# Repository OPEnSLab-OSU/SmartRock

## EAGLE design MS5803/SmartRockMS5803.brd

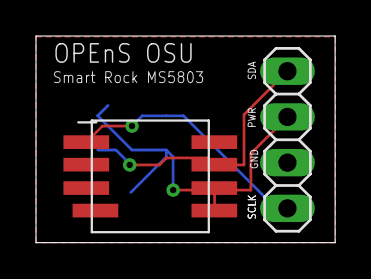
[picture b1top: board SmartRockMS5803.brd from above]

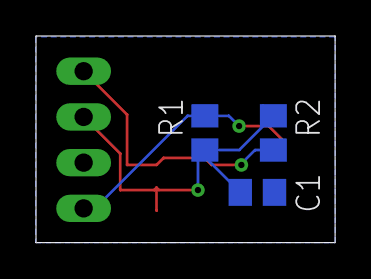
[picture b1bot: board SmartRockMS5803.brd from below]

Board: 2 copper layers, 16.6 x 11.5 mm, 5 parts (3 on the bottom side), 4 nets.

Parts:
C1: 100nF; C0805
JP1: 1X04
PRESSURE: MS5803-01BA; SMD
R1, R2: 7.7k; R0805

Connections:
GND: C1.1, JP1.3, PRESSURE.CSB, PRESSURE.GND
unnamed: C1.2, JP1.2, PRESSURE.PS, PRESSURE.VDD, R1.2, R2.2
unnamed: JP1.1, PRESSURE.SDI/SDA, R2.1
SCLK: JP1.4, PRESSURE.SCLK, R1.1

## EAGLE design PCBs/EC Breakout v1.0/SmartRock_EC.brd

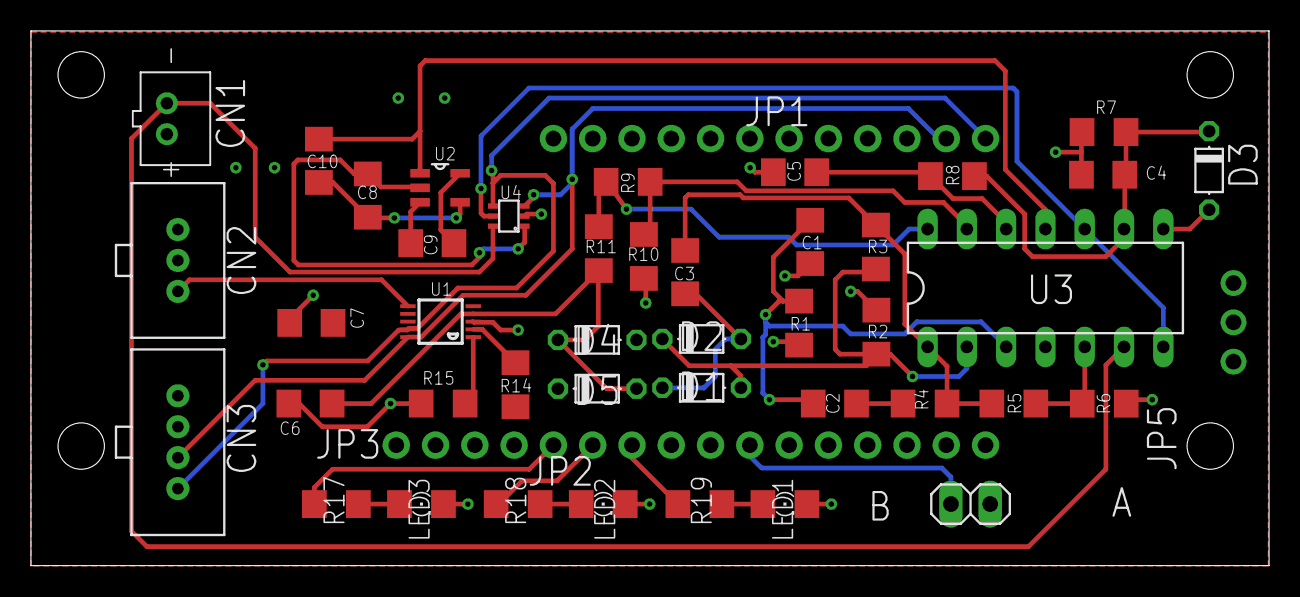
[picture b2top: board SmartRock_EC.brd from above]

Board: 2 copper layers, 80.0 x 34.6 mm, 46 parts (0 on the bottom side), 31 nets.

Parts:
C1, C2, C3: 100nF; C1206
C4, C5, C6, C7, C8, C9, C10: 1uF; C1206
CN1: JST-PH-2-THM
D1, D2, D3, D4, D5: 1N4001; D-5
IC2: TL074P; DIL14
JP1: 1X12-CB
JP2: 1X15-CB
JP3: 1X01-CLEANBIG
JP5: 1X03-CLEANBIG
LED1, LED2, LED3: 1206
R1, R4, R6: 1K; R1206
R2, R7, R9: 10K; R1206
R3: 22K; R1206
R5: 2K; R1206
R8, R11: 4.7K; R1206
R10: 5K; R1206
R14, R15: 10k; R1206
R17: 1k; R1206
R18, R19: 4.7k; R1206
REED: 1X02
U1: ADS1115IDGST; MSOP10
U2: TPS60400DBVR; SOT95P280X145-5N
U$1: AD5246
U$7: JST_4PIN_2MM
U$9: JST_3PIN_2MM

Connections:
ADDR: R15.1, U1.1
AIN2: U1.6, U$9.P$3
ALERT: R14.2, U1.2
AOUT: C6.2, D4.C, D5.A, R11.2, U1.4
ECSENSOR: CN1.2, IC2.6, U$1.B
GND: C1.2, C4.1, C5.1, C6.1, C7.1, C8.1, C10.1, CN1.1, D4.A, JP2.3, JP5.3, LED1.C, LED2.C, LED3.C, R1.1, R2.2, R6.1, R7.1, R10.2, R15.2, REED.2, U1.3, U2.4, U$1.GND, U$7.P$3, U$9.P$1
GPIOA0: JP2.4, R17.1
GPIOA1: JP2.5, R18.1
GPIOA2: JP2.6, R19.1
GPIOA5: JP2.9, REED.1
unnamed: C1.1, C2.1, IC2.3, R1.2
unnamed: C2.2, R4.2
unnamed: C3.2, IC2.1, R3.1, R4.1, R5.2
unnamed: D1.A, D2.C, IC2.2, R2.1, R3.2
unnamed: IC2.5, R5.1, R6.2
unnamed: C3.1, D1.C, D2.A
unnamed: C4.2, D3.C, IC2.9, R7.2, R8.2
unnamed: D3.A, IC2.8
unnamed: C5.2, IC2.12, R8.1
unnamed: IC2.13, R9.2, R10.1
unnamed: IC2.14, R9.1, R11.1
unnamed: LED3.A, R17.2
unnamed: LED2.A, R18.2
unnamed: LED1.A, R19.2
unnamed: C9.2, U2.5
unnamed: C9.1, U2.3
POT: IC2.7, IC2.10, U$1.W
SCL: JP1.2, U1.10, U$1.SCL, U$7.P$2
SDA: JP1.1, U1.9, U$1.SDA, U$7.P$1
VCC: C7.2, C8.2, D5.C, IC2.4, JP2.1, JP5.1, R14.1, U1.8, U2.2, U$1.VDD, U$7.P$4, U$9.P$2
VNEG: C10.2, IC2.11, U2.1
